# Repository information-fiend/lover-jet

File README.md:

<h2 align="center">
 
 Lover Jet: RC F-22 Raptor
</h2>
&nbsp;

> A lover, not a fighter. :warning: Not to mock or make light of warfare

A 4-channel RC system consisting of a Arduino Nano-based transmitter and a cardboard F-22 Raptor jet powered by brushless propulsion. It uses NRF24L01+ transceivers for communication. Made this as an introduction to aerospace systems, more to come :)

### 📷 Pictures

(Cardboard jet hasnt been cut out yet)

### BOM
|Qty| Device|	Link	|Cost	|
|---|-----|--------|-------|
1|Cardboard 60x85cm|Me|N/A
1|Motor 2205 2300kv|[Link](https://www.aliexpress.us/item/3256806652883904.html?spm=a2g0n.productlist.0.0.3bdd5422P3r9LE&browser_id=5652736715544da282a182e59dc7ecbe&aff_platform=msite&m_page_id=rultiifadhscaabg197d22a583a16e2eaa561bd8e4&gclid=&pdp_ext_f=%7B%22order%22%3A%22488%22%2C%22eval%22%3A%221%22%7D&pdp_npi=4%40dis%21USD%2122.05%210.99%21%21%21157.07%217.09%21%402103244617515776799154355e2e40%2112000038472336512%21sea%21US%210%21ABX&algo_pvid=5db91614-80cd-403c-8ae1-933cf5c6e285&_universallink=1&m_page_id=rultiifadhscaabg197d22a583a16e2eaa561bd8e4)|$0.99
1|Propeller 5045|[Link](https://www.aliexpress.us/item/3256806957215026.html?spm=a2g0o.productlist.main.5.70d93b02Syn12d&algo_pvid=ac7d01ee-8f18-4c90-b777-a92dccfda6ed&algo_exp_id=ac7d01ee-8f18-4c90-b777-a92dccfda6ed-4&pdp_ext_f=%7B%22order%22%3A%22136%22%2C%22eval%22%3A%221%22%7D&pdp_npi=4%40dis%21USD%217.58%212.50%21%21%2154.02%2117.83%21%402103244417518239498494110e881e%2112000039569802725%21sea%21US%212764046744%21X&curPageLogUid=dIzRwbvKSEBW&utparam-url=scene%3Asearch%7Cquery_from%3A)|$5.53
1|ESC 20A FMS|[Link](https://www.aliexpress.us/item/3256807612408276.html?spm=a2g0n.productlist.0.0.b2a87cbeDTMOMK&aff_platform=msite&m_page_id=rultiifadhscaabg197d23a674113284fef511ce56&gclid=&pdp_ext_f=%7B%22order%22%3A%22666%22%2C%22eval%22%3A%221%22%7D&pdp_npi=4%40dis%21USD%215.49%210.99%21%21%215.49%210.99%21%402101e7f617515787323374108ed735%2112000044240898274%21sea%21US%210%21ABX&algo_pvid=28674b5f-bf49-4b99-a495-a8c6fc2420fc)|$0.99
2|Servo 9g|[Link](https://www.aliexpress.us/item/3256805670877496.html?spm=a2g0n.productlist.0.0.48aa623fsyjOXx&aff_platform=msite&m_page_id=rultiifadhscaabg197d2769f7019407a08f125acd&gclid=&pdp_ext_f=%7B%22order%22%3A%22185%22%2C%22eval%22%3A%221%22%7D&pdp_npi=4%40dis%21USD%2121.61%210.99%21%21%21153.93%217.05%21%40210330dd17515826788378188e912f%2112000034594693909%21sea%21US%210%21ABX&algo_pvid=39e5eabd-9ab9-4f93-8d7f-380deeeda818)|$0.99
1|NRF24L01 receiver module|[Link](https://www.aliexpress.us/item/3256807924390952.html?spm=a2g0o.productlist.main.2.386dbHtNbHtN1f&algo_pvid=dc0878e2-ad5b-433c-b703-2730000ec275&algo_exp_id=dc0878e2-ad5b-433c-b703-2730000ec275-1&pdp_ext_f=%7B%22order%22%3A%221%22%2C%22eval%22%3A%221%22%7D&pdp_npi=4%40dis%21USD%2121.01%213.25%21%21%21149.93%2123.15%21%402101d9ef17522670686454234eb32f%2112000043824601371%21sea%21US%212764046744%21X&curPageLogUid=yDOKpiqBXnQ1&utparam-url=scene%3Asearch%7Cquery_from%3A)|$3.64
2|7.4v 450mah li-po battery|[Link](https://www.aliexpress.us/item/3256807759429745.html?spm=a2g0o.productlist.main.3.7c17hs5ghs5gcA&algo_pvid=ac9076dc-3f48-43c0-b60b-54fa5cffb2a3&algo_exp_id=ac9076dc-3f48-43c0-b60b-54fa5cffb2a3-2&pdp_ext_f=%7B%22order%22%3A%2217%22%2C%22eval%22%3A%221%22%7D&pdp_npi=4%40dis%21USD%2145.70%2111.58%21%21%21326.20%2182.67%21%402101efeb17522592827473602ea157%2112000042990139180%21sea%21US%212764046744%21X&curPageLogUid=6ByXfxuSc0AG&utparam-url=scene%3Asearch%7Cquery_from%3A)|$11.58
2|Arduino nano v3.0|[Link](https://www.amazon.com/LAFVIN-Board-ATmega328P-Micro-Controller-Arduino/dp/B07G99NNXL?crid=1EAG34EPIZNYD&dib=eyJ2IjoiMSJ9.KnW4qA_nYCmhNNFB9Jor2mZYks7foDh660Md2JMIWjnn_tQQUai_-ZHZIFz_5LyghdyjHvBEbwSdBb1weFNh-5VdHUEL41jfYod-rEnw_5vy2t_LA9AOCXK-PjPKdHW_huGHSkKDVRCONeqy8S9eOgmfnr6r-uyZ_VWKlqvf3WxGtWpKnUSIbX6SL1HFFsc-7djjZocvEOWnm766VUsDWfup5s3nQOYO5fTOMkZL6r0.504UJmXaMyXSFyYu5wM2_YnldD7sP5hOD4wF1xbUCjk&dib_tag=se&keywords=arduino+nano+v3&qid=1751134437&sprefix=arduino+nano+v3%2Caps%2C143&sr=8-1&xpid=BLck2ap9v-6h8)|$15.99
2|KY-023 joystick|[Link](https://www.aliexpress.us/item/3256807375670744.html?spm=a2g0o.productlist.main.2.731d1b6bFiOkFE&algo_pvid=48840e47-dfbc-4486-94fc-888a6d3b0aa0&algo_exp_id=48840e47-dfbc-4486-94fc-888a6d3b0aa0-1&pdp_ext_f=%7B%22order%22%3A%22419%22%2C%22eval%22%3A%221%22%7D&pdp_npi=4%40dis%21USD%211.31%211.31%21%21%219.36%219.36%21%402103247017518234826923714e2950%2112000041302774768%21sea%21US%212764046744%21X&curPageLogUid=HD9hnZuoxTGf&utparam-url=scene%3Asearch%7Cquery_from%3A)|$1.77
1|NRF24L01 + PA|[Link](https://www.aliexpress.us/item/3256805495903750.html?spm=a2g0o.productlist.main.2.10a8CcuGCcuGbp&algo_pvid=b8a78c33-ddba-409a-8542-f9fa9484b47c&algo_exp_id=b8a78c33-ddba-409a-8542-f9fa9484b47c-1&pdp_ext_f=%7B%22order%22%3A%221797%22%2C%22eval%22%3A%221%22%7D&pdp_npi=4%40dis%21USD%211.37%211.37%21%21%219.73%219.73%21%40212a6e2917518233391448007ef4e2%2112000033996194288%21sea%21US%212764046744%21X&curPageLogUid=GsFdteWDsalm&utparam-url=scene%3Asearch%7Cquery_from%3A)|$2.30
1|Single Pole Single Throw (SPST) Switch|[Link](https://www.aliexpress.us/item/3256808934087455.html?spm=a2g0o.productlist.main.2.1a3121d9Kixaqw&algo_pvid=28ceaca7-ff60-45f0-b66f-6837c0d55d8d&algo_exp_id=28ceaca7-ff60-45f0-b66f-6837c0d55d8d-1&pdp_ext_f=%7B%22order%22%3A%222%22%2C%22eval%22%3A%221%22%7D&pdp_npi=4%40dis%21USD%211.48%211.48%21%21%2110.54%2110.54%21%402101c80217522010231448540e2372%2112000047985280452%21sea%21US%212764046744%21X&curPageLogUid=1zAMOos0XsEP&utparam-url=scene%3Asearch%7Cquery_from%3A)|$1.48
1|EC11 rotary encoder|[Link](https://www.aliexpress.us/item/3256807457768762.html?spm=a2g0o.productlist.main.5.3cca2c6aoOR5bo&algo_pvid=9f93f91b-e0b3-40b3-b244-2e4697363354&algo_exp_id=9f93f91b-e0b3-40b3-b244-2e4697363354-4&pdp_ext_f=%7B%22order%22%3A%22533%22%2C%22eval%22%3A%221%22%7D&pdp_npi=4%40dis%21USD%212.15%212.15%21%21%212.15%212.15%21%402101eac917518237424086563e44af%2112000041630839416%21sea%21US%212764046744%21X&curPageLogUid=d6OsA5KxRH80&utparam-url=scene%3Asearch%7Cquery_from%3A)|$2.15
1|Voltage regulator 7805|[Link](https://www.aliexpress.us/item/3256807345258850.html?spm=a2g0o.productlist.main.1.167b3a8f9DAJyj&aem_p4p_detail=2025071113535010332751057567280000641333&algo_pvid=80f28123-5950-4938-9758-a35f7eaadfd5&algo_exp_id=80f28123-5950-4938-9758-a35f7eaadfd5-0&pdp_ext_f=%7B%22order%22%3A%22728%22%2C%22eval%22%3A%221%22%7D&pdp_npi=4%40dis%21USD%211.69%211.64%21%21%2112.06%2111.73%21%40210308a417522672304563947e22eb%2112000041177898915%21sea%21US%212764046744%21X&curPageLogUid=4J2FkPGaP4Ya&utparam-url=scene%3Asearch%7Cquery_from%3A&search_p4p_id=2025071113535010332751057567280000641333_1)|$1.95
2|100 µF capacitor|[Link](https://www.aliexpress.us/item/3256805372329013.html?spm=a2g0o.productlist.main.1.18ae3acdstcoJ9&aem_p4p_detail=202507111144151240583748424440001479146&algo_pvid=629a8b22-af45-4e69-99d4-c403317637bd&algo_exp_id=629a8b22-af45-4e69-99d4-c403317637bd-0&pdp_ext_f=%7B%22order%22%3A%22714%22%2C%22eval%22%3A%221%22%7D&pdp_npi=4%40dis%21USD%212.08%211.99%21%21%212.08%211.99%21%402103244b17522594553888213e979e%2112000033538166697%21sea%21US%212764046744%21X&curPageLogUid=Yik1haHNONSo&utparam-url=scene%3Asearch%7Cquery_from%3A&search_p4p_id=202507111144151240583748424440001479146_1)|$1.99
2|10 µF capacitor|[Link](https://www.aliexpress.us/item/3256805372329013.html?spm=a2g0o.productlist.main.1.18ae3acdstcoJ9&aem_p4p_detail=202507111144151240583748424440001479146&algo_pvid=629a8b22-af45-4e69-99d4-c403317637bd&algo_exp_id=629a8b22-af45-4e69-99d4-c403317637bd-0&pdp_ext_f=%7B%22order%22%3A%22714%22%2C%22eval%22%3A%221%22%7D&pdp_npi=4%40dis%21USD%212.08%211.99%21%21%212.08%211.99%21%402103244b17522594553888213e979e%2112000033538166697%21sea%21US%212764046744%21X&curPageLogUid=Yik1haHNONSo&utparam-url=scene%3Asearch%7Cquery_from%3A&search_p4p_id=202507111144151240583748424440001479146_1)|$1.99
1|AMS1117-3.3v|[Link](https://www.aliexpress.us/item/3256808067206574.html?spm=a2g0o.productlist.main.2.7e8b4dc96CObTZ&algo_pvid=df719208-c5a3-4e6b-a061-9c704f1fd582&algo_exp_id=df719208-c5a3-4e6b-a061-9c704f1fd582-1&pdp_ext_f=%7B%22order%22%3A%2223%22%2C%22eval%22%3A%221%22%7D&pdp_npi=4%40dis%21USD%213.93%211.96%21%21%2128.06%2114.03%21%402103205117522672582144188e5cb8%2112000044384344254%21sea%21US%212764046744%21X&curPageLogUid=mFaXF7pfFPFI&utparam-url=scene%3Asearch%7Cquery_from%3A)|$1.99
1|pcb| |$20.00
| | | |= $77.32

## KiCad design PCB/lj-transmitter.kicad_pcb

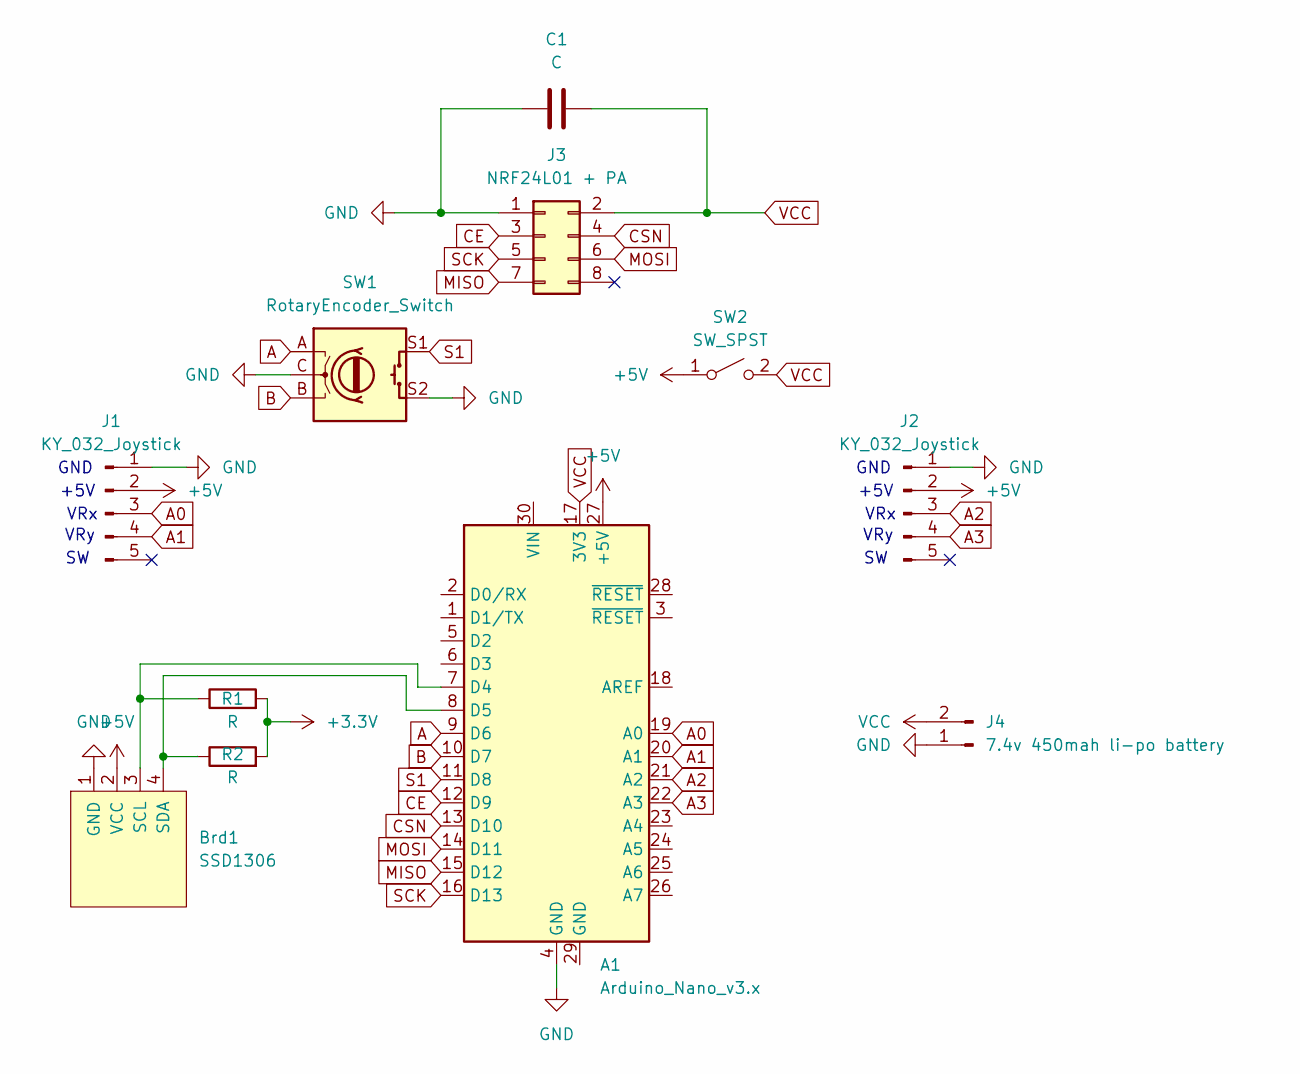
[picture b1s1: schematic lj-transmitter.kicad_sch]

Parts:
A1: Arduino_Nano_v3.x; Arduino_Nano
Brd1: SSD1306; 128x64OLED
C1: C; CP_Radial_D8.0mm_P5.00mm
J1, J2: KY_032_Joystick; PinHeader_1x05_P1.00mm_Vertical
J3: NRF24L01 + PA; nRF24L01_Breakout
J4: 7.4v 450mah li-po battery; BatteryHolder_Keystone_3034_1x20mm
R1, R2: R; R_Axial_DIN0207_L6.3mm_D2.5mm_P7.62mm_Horizontal
SW1: RotaryEncoder_Switch; RotaryEncoder_Alps_EC11E-Switch_Vertical_H20mm_CircularMoun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
SW2: SW_SPST; SW_CW_GPTS203211B

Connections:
+3.3V: R1.2, R2.2
+5V: A1.27 (+5V), Brd1.2 (VCC), J1.2, J2.2, SW2.1 (A)
A: A1.9 (D6), SW1.A
A0: A1.19 (A0), J1.3
A1: A1.20 (A1), J1.4
A2: A1.21 (A2), J2.3
A3: A1.22 (A3), J2.4
B: A1.10 (D7), SW1.B
CE: A1.12 (D9), J3.3
CSN: A1.13 (D10), J3.4
GND: A1.4 (GND), Brd1.1 (GND), C1.1, J1.1, J2.1, J3.1, J4.1, SW1.C, SW1.S2
MISO: A1.15 (D12), J3.7
MOSI: A1.14 (D11), J3.6
unnamed: A1.7 (D4), Brd1.3 (SCL), R1.1
unnamed: A1.8 (D5), Brd1.4 (SDA), R2.1
S1: A1.11 (D8), SW1.S1
SCK: A1.16 (D13), J3.5
VCC: A1.17 (3V3), C1.2, J3.2, J4.2, SW2.2 (B)

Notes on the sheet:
VRy
+5V
GND
VRx

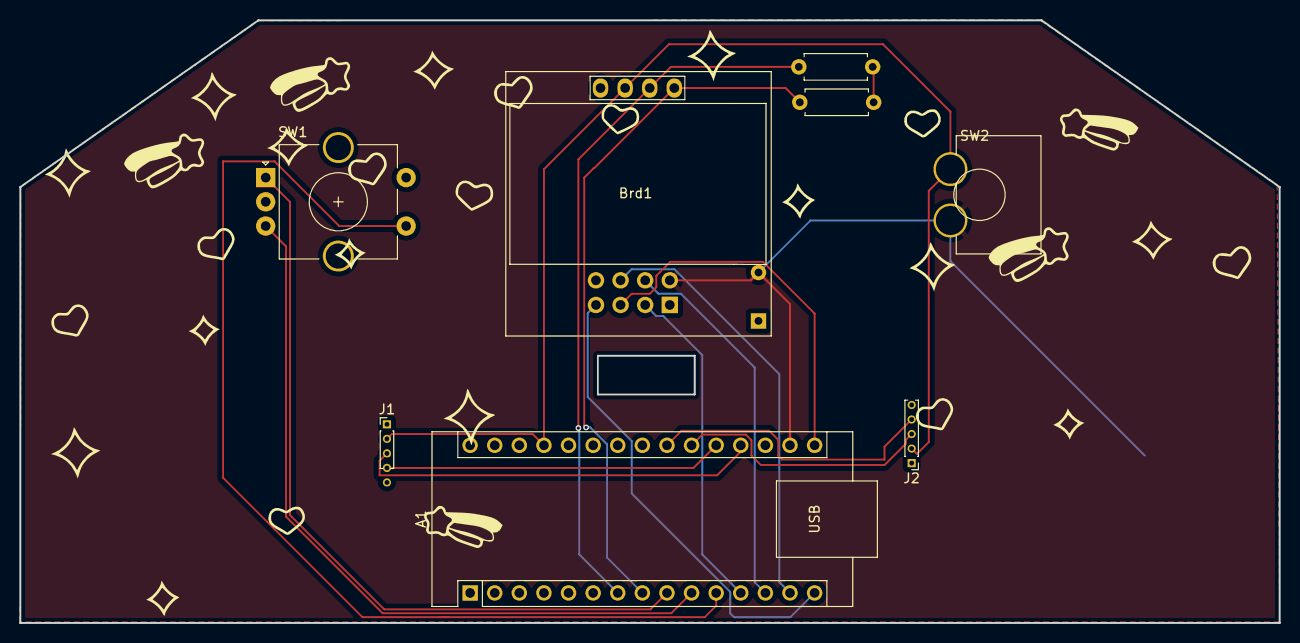
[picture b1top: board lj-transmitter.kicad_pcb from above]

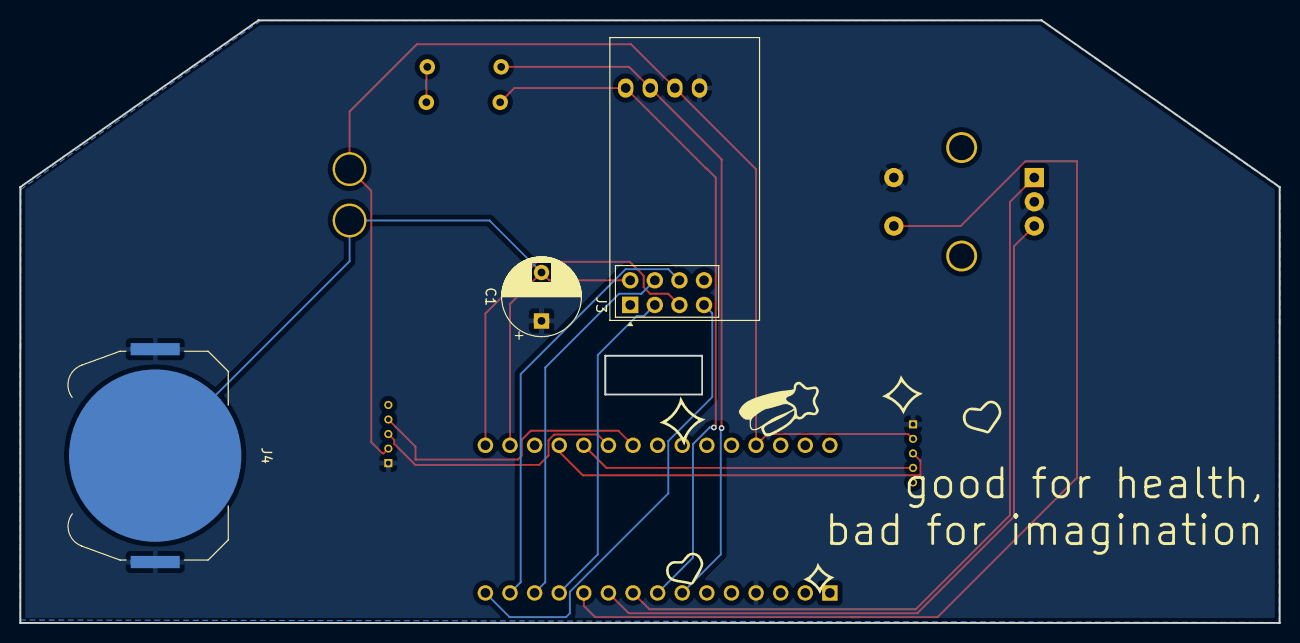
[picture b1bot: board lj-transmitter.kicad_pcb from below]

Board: 2 copper layers, 130.0 x 62.2 mm, 11 parts (3 on the bottom side), 18 nets.

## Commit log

2025-06-28 Create 1
2025-06-28 Create 2
2025-06-28 Create 3
2025-06-28 this is what'll be cutout on cardboard
2025-06-29 Add files via upload
    diagram 1 is from YT, shows the wires a lil better
2025-06-29 added CAD
2025-07-11 updated pcb
2025-07-11 updated wiring diagram
2025-07-11 add code
2025-07-11 final BOM
2025-07-11 add BOM
2025-11-22 "warefare"?? how did i not notice lol
